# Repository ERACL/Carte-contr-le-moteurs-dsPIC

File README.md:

Carte contrôle moteurs dsPIC
============================

Carte contrôle moteurs dsPIC - Contient le code pour le dsPIC et la CAO KiCAD de la carte

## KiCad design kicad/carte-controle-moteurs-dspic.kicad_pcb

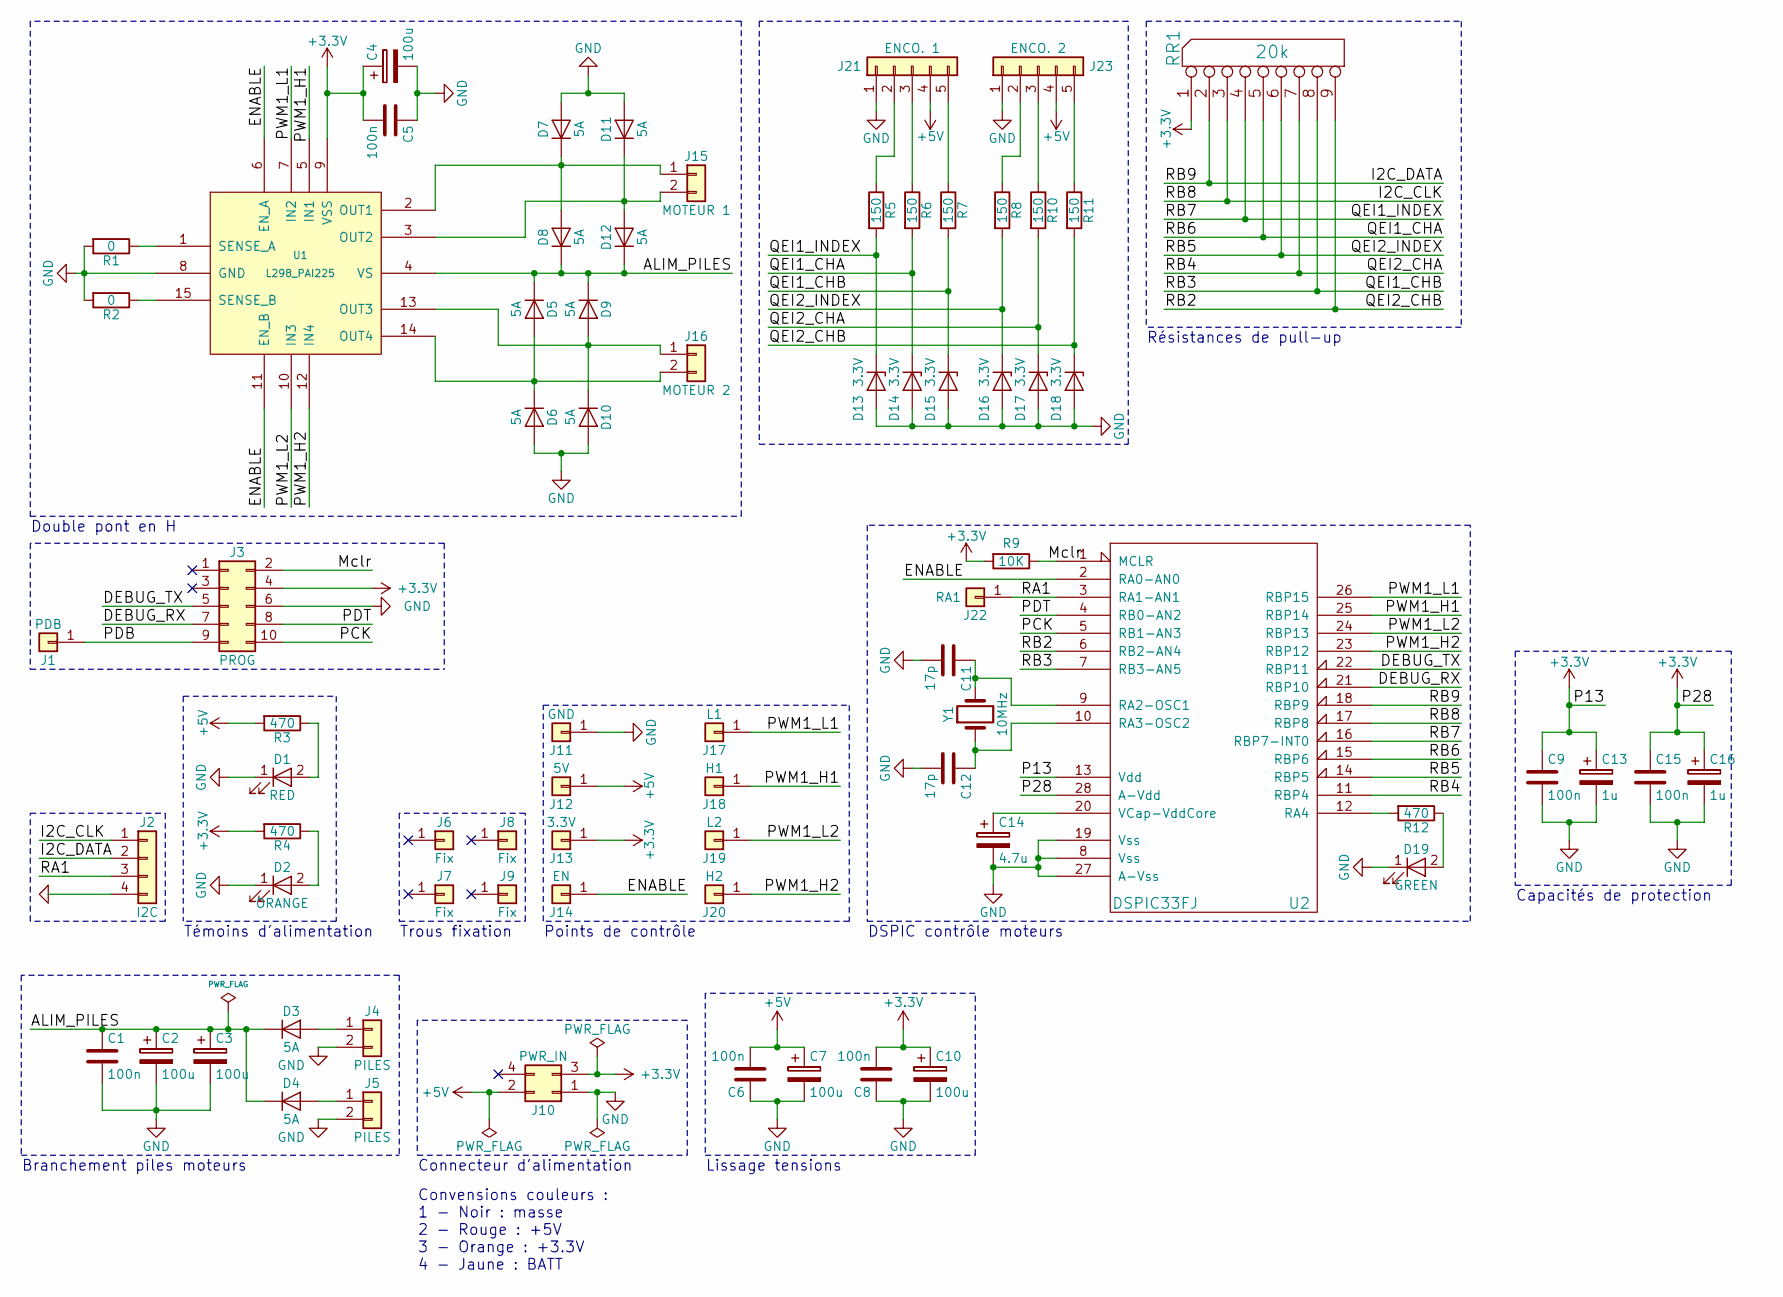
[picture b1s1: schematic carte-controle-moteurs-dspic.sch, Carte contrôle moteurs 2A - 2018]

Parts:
C1, C5, C6, C8, C9, C15: 100n; C_Rect_L7.0mm_W3.5mm_P2.50mm_P5.00mm
C2, C3, C4, C7, C10: 100u; CP_Radial_D10.0mm_P2.50mm_P5.00mm
C11, C12: 17p; C_Rect_L7.0mm_W3.5mm_P2.50mm_P5.00mm
C13, C16: 1u; CP_Radial_D10.0mm_P2.50mm_P5.00mm
C14: 4.7u; CP_Radial_D10.0mm_P2.50mm_P5.00mm
D1: RED; LED_D3.0mm
D2: ORANGE; LED_D3.0mm
D3, D4, D5, D6, D7, D8, D9, D10, D11, D12: 5A; D_A-405_P10.16mm_Horizontal
D13, D14, D15, D16, D17, D18: 3.3V; D_A-405_P10.16mm_Horizontal
D19: GREEN; LED_D3.0mm
J1: PDB; Measurement_Point_Round-TH_Small
J2: I2C; KK_4C
J3: PROG; Pin_Header_Straight_2x05_Pitch2.54mm
J4, J5: PILES; Molex_MiniFit-JR-5569-02A2_2x01x4.20mm_Angled
J6, J7, J8, J9: Fix; MountingHole_3.2mm_M3_Pad
J10: PWR_IN; Molex_MiniFit-JR-5569-04A2_2x02x4.20mm_Angled
J11: GND; Measurement_Point_Round-TH_Small
J12: 5V; Measurement_Point_Round-TH_Small
J13: 3.3V; Measurement_Point_Round-TH_Small
J14: EN; Measurement_Point_Round-TH_Small
J15: MOTEUR 1; Molex_MiniFit-JR-5569-02A2_2x01x4.20mm_Angled
J16: MOTEUR 2; Molex_MiniFit-JR-5569-02A2_2x01x4.20mm_Angled
J17: L1; Measurement_Point_Round-TH_Small
J18: H1; Measurement_Point_Round-TH_Small
J19: L2; Measurement_Point_Round-TH_Small
J20: H2; Measurement_Point_Round-TH_Small
J21: ENCO. 1; Pin_Header_Angled_1x05_Pitch2.54mm
J22: RA1; Measurement_Point_Round-TH_Small
J23: ENCO. 2; Pin_Header_Angled_1x05_Pitch2.54mm
R1, R2: 0; R_Axial_DIN0204_L3.6mm_D1.6mm_P7.62mm_Horizontal
R3, R4, R12: 470; R_Axial_DIN0204_L3.6mm_D1.6mm_P7.62mm_Horizontal
R5, R6, R7, R8, R10, R11: 150; R_Axial_DIN0204_L3.6mm_D1.6mm_P7.62mm_Horizontal
R9: 10K; R_Axial_DIN0204_L3.6mm_D1.6mm_P7.62mm_Horizontal
RR1: 20k; R_Array_SIP9
U1: L298_PAI225; Multiwatt-15_Vertical_StaggeredType1
U2: DSPIC33FJ; DIP-28_W7.62mm
Y1: 10MHz; Crystal_HC18-U_Vertical

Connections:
+3V3: C4.1, C5.2, C8.2, C9.1, C10.1, C13.1, C15.1, C16.1, J3.4, J10.3, J13.1, R4.2, R9.2, RR1.1 (COM), U1.9 (VSS), U2.13 (Vdd), U2.28 (A-Vdd)
+5V: C6.2, C7.1, J10.2, J12.1, J21.4, J23.4, R3.2
/ALIM_PILES: C1.1, C2.1, C3.1, D3.1 (K), D4.1 (K), D5.1 (K), D8.1 (K), D9.1 (K), D12.1 (K), U1.4 (VS)
/DEBUG_RX: J3.7, U2.21 (RBP10)
/DEBUG_TX: J3.5, U2.22 (RBP11)
/ENABLE: J14.1, U1.6 (EN_A), U1.11 (EN_B), U2.2 (RA0-AN0)
/I2C_CLK: J2.1, RR1.3, U2.17 (RBP8)
/I2C_DATA: J2.2, RR1.2, U2.18 (RBP9)
/Mclr: J3.2, R9.1, U2.1 (MCLR)
/PCK: J3.10, U2.5 (RB1-AN3)
/PDB: J1.1, J3.9
/PDT: J3.8, U2.4 (RB0-AN2)
/PWM1_H1: J18.1, U1.5 (IN1), U2.25 (RBP14)
/PWM1_H2: J20.1, U1.12 (IN4), U2.23 (RBP12)
/PWM1_L1: J17.1, U1.7 (IN2), U2.26 (RBP15)
/PWM1_L2: J19.1, U1.10 (IN3), U2.24 (RBP13)
/QEI1_CHA: D14.1 (K), R6.2, RR1.5, U2.15 (RBP6)
/QEI1_CHB: D15.1 (K), R7.2, RR1.8, U2.7 (RB3-AN5)
/QEI1_INDEX: D13.1 (K), R5.2, RR1.4, U2.16 (RBP7-INT0)
/QEI2_CHA: D17.1 (K), R10.2, RR1.7, U2.11 (RBP4)
/QEI2_CHB: D18.1 (K), R11.2, RR1.9, U2.6 (RB2-AN4)
/QEI2_INDEX: D16.1 (K), R8.2, RR1.6, U2.14 (RBP5)
/RA1: J2.3, J22.1, U2.3 (RA1-AN1)
GND: C1.2, C2.2, C3.2, C4.2, C5.1, C6.1, C7.2, C8.1, C9.2, C10.2, C11.2, C12.2, C13.2, C14.2, C15.2, C16.2, D1.1 (K), D2.1 (K), D6.2 (A), D7.2 (A), D10.2 (A), D11.2 (A), D13.2 (A), D14.2 (A), D15.2 (A), D16.2 (A), D17.2 (A), D18.2 (A), D19.1 (K), J2.4, J3.6, J4.2, J5.2, J10.1, J11.1, J21.1, J23.1, R1.2, R2.2, U1.8 (GND), U2.8 (Vss), U2.19 (Vss), U2.27 (A-Vss)
unnamed: C11.1, U2.9 (RA2-OSC1), Y1.2
unnamed: C12.1, U2.10 (RA3-OSC2), Y1.1
unnamed: C14.1, U2.20 (VCap-VddCore)
unnamed: D1.2 (A), R3.1
unnamed: D2.2 (A), R4.1
unnamed: D3.2 (A), J4.1
unnamed: D4.2 (A), J5.1
unnamed: D5.2 (A), D6.1 (K), J16.2, U1.14 (OUT4)
unnamed: D7.1 (K), D8.2 (A), J15.1, U1.2 (OUT1)
unnamed: D9.2 (A), D10.1 (K), J16.1, U1.13 (OUT3)
unnamed: D11.1 (K), D12.2 (A), J15.2, U1.3 (OUT2)
unnamed: D19.2 (A), R12.1
unnamed: J21.2, R5.1
unnamed: J21.3, R6.1
unnamed: J21.5, R7.1
unnamed: J23.2, R8.1
unnamed: J23.3, R10.1
unnamed: J23.5, R11.1
unnamed: R1.1, U1.1 (SENSE_A)
unnamed: R2.1, U1.15 (SENSE_B)
unnamed: R12.2, U2.12 (RA4)

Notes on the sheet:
Trous fixation
Double pont en H
Branchement piles moteurs
Points de contrôle
Témoins d'alimentation
Résistances de pull-up
DSPIC contrôle moteurs
Connecteur d'alimentation
Convensions couleurs : 1 - Noir : masse 2 - Rouge : +5V 3 - Orange : +3.3V 4 - Jaune : BATT
Lissage tensions
Capacités de protection

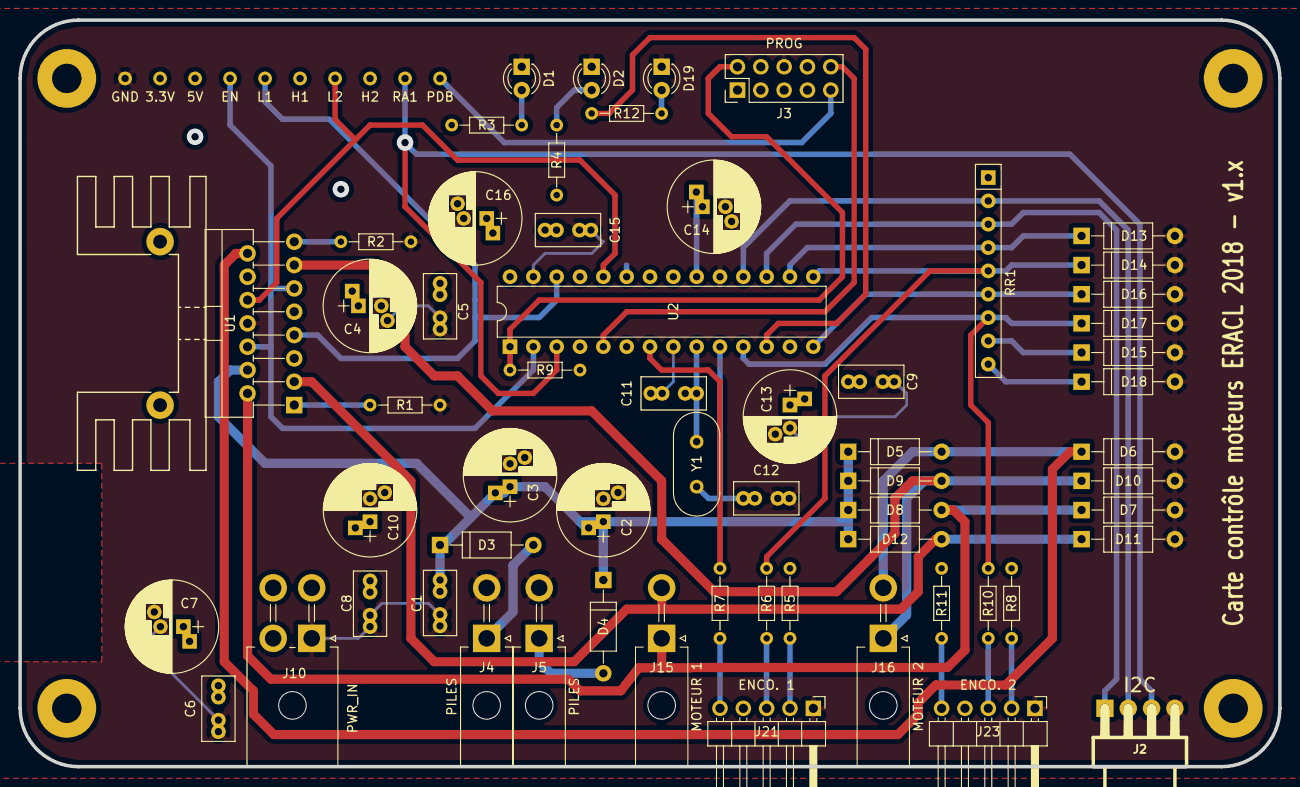
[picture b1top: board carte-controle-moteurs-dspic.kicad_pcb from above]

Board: 4 copper layers, 137.2 x 81.3 mm, 74 parts (0 on the bottom side), 45 nets.

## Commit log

2018-01-26 Mise en forme du fichier README
2018-02-11 Ajout des fichiers de l'année dernière (2016-2017)
2018-02-11 Initial commit nouvelle carte
2018-02-11 Placement connecteurs, processeur et L298
2018-02-11 Placement de quasi tous les composants
2018-02-11 Importation composants sur typon
2018-02-11 Deuxième partie du tracé des pistes, reste à connecter GND et les alims
2018-02-11 Renommé DEBUG_1/2 en TX et RX
2018-02-11 Modification connecteur programmation
2018-02-11 Modification du connecteur de programmation
2018-02-11 Ajout empreintes connecteurs
2018-02-11 Correctif : condensateur 4.7u n'était pas en polarisé
2018-02-11 Contour PCB le plus grand possible
2018-02-11 Finition du typon
2018-02-11 Typon quasi-prêt, reste à mettre les plans de masse
2018-02-11 Changement empreintes
2018-02-11 Début de traçage des pistes
2018-02-11 Placement de tous les composants
2018-02-11 Réalisation du typon
2018-02-11 Mise à jour des autres fichiers
2018-02-11 Ajout zone puce RFID et nom de la carte
2018-02-11 Ajout des trous de fixation
2018-02-11 Mise en conformité des noms et emplacements des fichiers KiCAD
2018-02-12 Modification du gitignore (recopie de celui de la carte alim)
2018-02-13 Mise à jour des fichiers pour la nouvelle version de KiCAD
2018-02-13 Finalisation du typon
2018-02-14 Pré-validation CAO KiCAD
2018-02-15 Changement empreintes résistances
2018-02-15 Mise à jour du typon avec les nouvelles empreintes
2018-02-15 Ignorer dossier export pour gerber
2018-02-15 Optimisation de l'emplacement des composants et de la sérigraphie
2018-02-15 Optimisation du tracé des pistes et des plans et validation typon
2018-02-16 Mise à jour de la version dans les cartouches et la sérigraphie
2018-02-18 Ajout d'un lot de capacités pour la patte 28 du DsPIC
